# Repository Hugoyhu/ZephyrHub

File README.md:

# ZephyrHub

ZephyrHub is a simple four port USB 2.0 Hub designed for the [Hacker Zephyr](https://zephyr.hackclub.com), a 10-day hackathon where hack clubbers went across the country from HC HQ in Shelburne VT to SpaceX in LA.

The board is modeled off the Superdome, one of the train cars chartered for the journey. It allows for a reversible USB2/3 Type C cable in, and outputs four USB2 Type A ports. 

The design files, schematic, and BOM/ordering info are available in this repo. Files were designed in KiCAD v5 and are forward-compatible to KiCAD v6+. An image of the schematic and a .zip of the gerbers are also provided.

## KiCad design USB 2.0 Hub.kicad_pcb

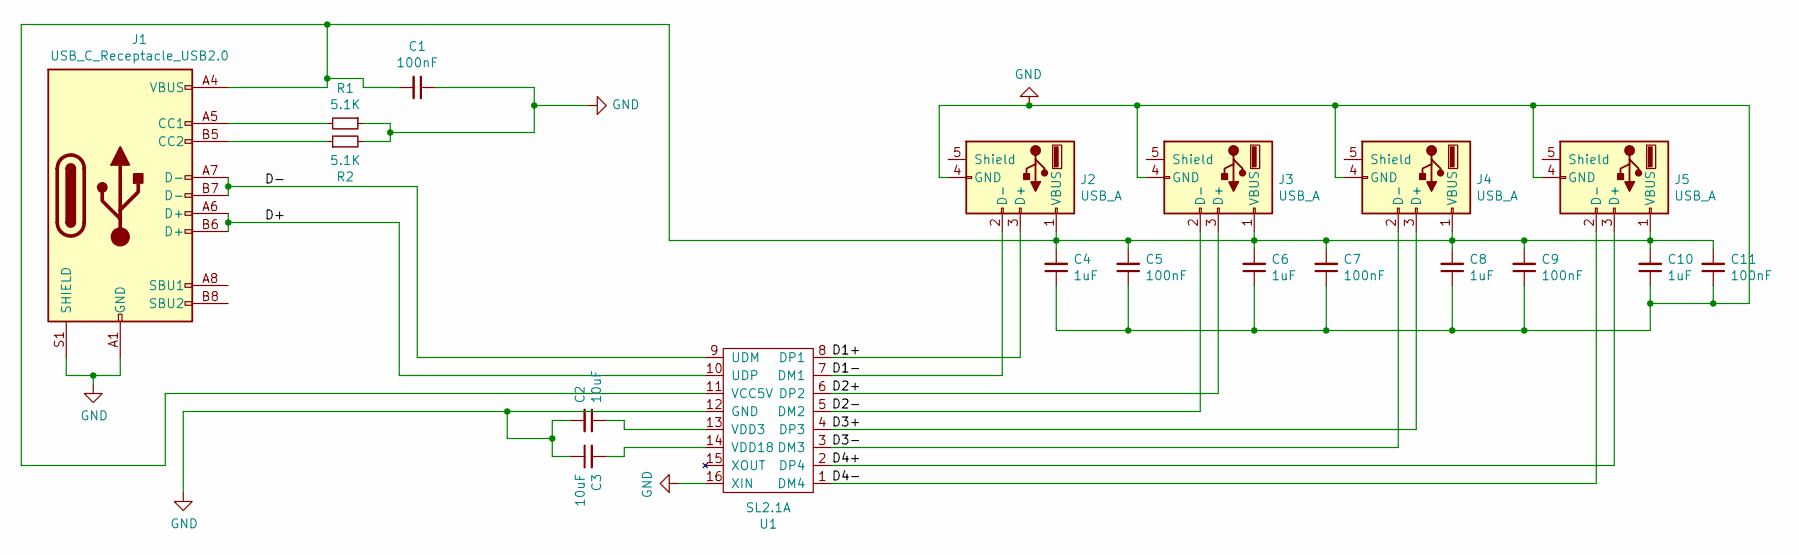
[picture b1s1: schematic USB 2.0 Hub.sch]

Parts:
C1, C5, C7, C9, C11: 100nF; C_0805_2012Metric_Pad1.18x1.45mm_HandSolder
C2, C3: 10uF; C_0805_2012Metric_Pad1.18x1.45mm_HandSolder
C4, C6, C8, C10: 1uF; C_0805_2012Metric_Pad1.18x1.45mm_HandSolder
J1: USB_C_Receptacle_USB2.0; USB_C_Receptacle_GCT_USB4085
J2, J3, J4, J5: USB_A; USBA_THT_SMD
R1, R2: 5.1K; R_0805_2012Metric_Pad1.20x1.40mm_HandSolder
U1: SL2.1A; SOIC-16_4.55x10.3mm_P1.27mm

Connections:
/D1+: J2.3 (D+), U1.8 (DP1)
/D1-: J2.2 (D-), U1.7 (DM1)
/D2+: J3.3 (D+), U1.6 (DP2)
/D2-: J3.2 (D-), U1.5 (DM2)
/D3+: J4.3 (D+), U1.4 (DP3)
/D3-: J4.2 (D-), U1.3 (DM3)
/D4+: J5.3 (D+), U1.2 (DP4)
/D4-: J5.2 (D-), U1.1 (DM4)
/D+: J1.A6 (D+), J1.B6 (D+), U1.10 (UDP)
/D-: J1.A7 (D-), J1.B7 (D-), U1.9 (UDM)
GND: C1.1, C2.2, C3.1, C4.1, C5.1, C6.1, C7.1, C8.1, C9.1, C10.1, C11.1, J1.A1 (GND), J1.A12 (GND), J1.B1 (GND), J1.B12 (GND), J1.S1 (SHIELD), J2.4 (GND), J3.4 (GND), J4.4 (GND), J5.4 (GND), R1.1, R2.2, U1.12 (GND), U1.16 (XIN)
unnamed: C1.2, C4.2, C5.2, C6.2, C7.2, C8.2, C9.2, C10.2, C11.2, J1.A4 (VBUS), J1.A9 (VBUS), J1.B4 (VBUS), J1.B9 (VBUS), J2.1 (VBUS), J3.1 (VBUS), J4.1 (VBUS), J5.1 (VBUS), U1.11 (VCC5V)
unnamed: C2.1, U1.13 (VDD3)
unnamed: C3.2, U1.14 (VDD18)
unnamed: J1.A5 (CC1), R1.2
unnamed: J1.B5 (CC2), R2.1

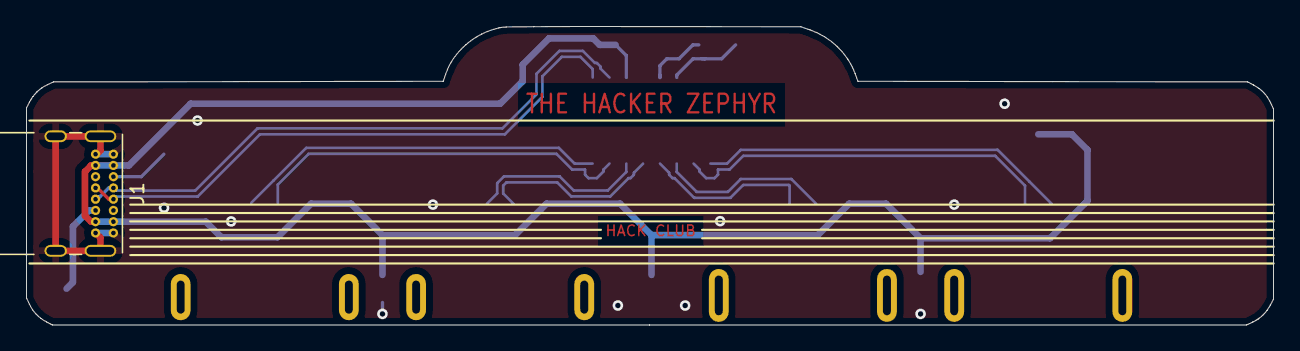
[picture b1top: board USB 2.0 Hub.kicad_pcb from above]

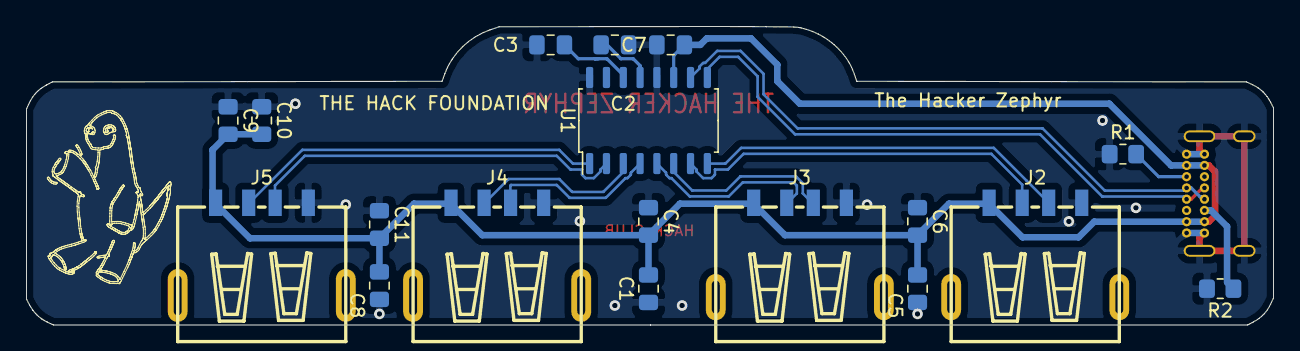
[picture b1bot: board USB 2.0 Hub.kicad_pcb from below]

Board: 2 copper layers, 94.2 x 22.5 mm, 19 parts (18 on the bottom side), 16 nets.

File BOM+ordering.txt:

BOM:

4x USB A connectors; LCSC; https://lcsc.com/product-detail/USB-Connectors_Jing-Extensio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
1x SL2.1A; LCSC; https://lcsc.com/product-detail/USB-ICs_CoreChips-SL2-1A_C19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
1x GCT USB-4085; Mouser; https://www.mouser.com/ProductDetail/GCT/USB4085-GF-A?qs=%2F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
2x 5.1K 0805 Resistor; Generic
2x 10uF 0805 MLCC Capacitor; Generic
4x 1uF 0805 MLCC Capacitor; Generic
5x 100nF 0805 MLCC Capacitor; Generic

Ordering information:

1.2mm FR-4 PCB, double sided, 1oz copper, Matte Black Soldermask, ENIG finish, 94.18mm x 22.54mm

Please use RoHS compliant parts, PCBs, and equipment.

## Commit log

2021-07-27 Add files via upload
    add kicad files- more coming soon
